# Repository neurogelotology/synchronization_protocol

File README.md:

# Synchronization Protocol

This repository provides files associated with our protocol paper about signal synchronization.

Dagher & Ishiyama (2023) STAR Protocols.

Example data are available:

Dagher, Sarah; Ishiyama, Shimpei (2023), “Signal synchronization in systems neuroscience (example data)”, Mendeley Data, V1, doi: 10.17632/98rzkwy8s6.1

## Pulse generator PCB

Printed circuit board (PCB) of the pulse generator is provided as KiCad files in the Pulse_Generator_PCB folder.

Printing the PCB can be outsourced to companies such as Aisler. Aisler accepts KiCad files directly.

## Pulse generator software

Codes necessary for the pulse generator are under the Pulse_Generator_software folder.

MATLAB files are necessary to trigger the pulse generator from MATLAB.

**exampleTimer.m** demonstrates an example use of triggering the pulse generator from MATLAB.

ArduinoLibrary\pulseGen folder contains Arduino files to setup the main Teensy board of the pulse generator.

myPulses folder contains an Arduino file to configure custom settings for each channel of the pulse generator.

## Sync TTL analysis

syncTTL folder contains MATLAB functions to extract TTL times from each signal.

**getAudioTTL_demo.m** extracts TTL rise times [s] from the least significant bit of a .wav file recorded by Avisoft devices. Times are based on the sample positions in the .wav file.

**getNlxTTL_demo.m**  extracts TTL rise times [s] from a Events.nev file created by Neuralynx Cheetah software. Users may need to adjust `TTLeventID` and `bitpos` dependent on the Neuralynx device used. Times are based on the timestamps of the Neuralynx device.

**getVideoTTL_demo.m** extracts TTL rise times [s] from a .csv file created by Bonsai with our configuration for the FLIR cameras. Times are based on the timestamps of the FLIR camera.

**sync_pulse_analysis.mlx** demonstrates sync pulse analysis to verify the validity of a recording. Example data are provided in Example_data folder.

## Bonsai file

**TwoCam.bonsai** demonstrates an example setting for video recording with two FLIR cameras, monitoring real-time TTL status and drop frames, embedding frame ID in the video frames, and exporting timestamp and TTL status of each frame as .csv files.

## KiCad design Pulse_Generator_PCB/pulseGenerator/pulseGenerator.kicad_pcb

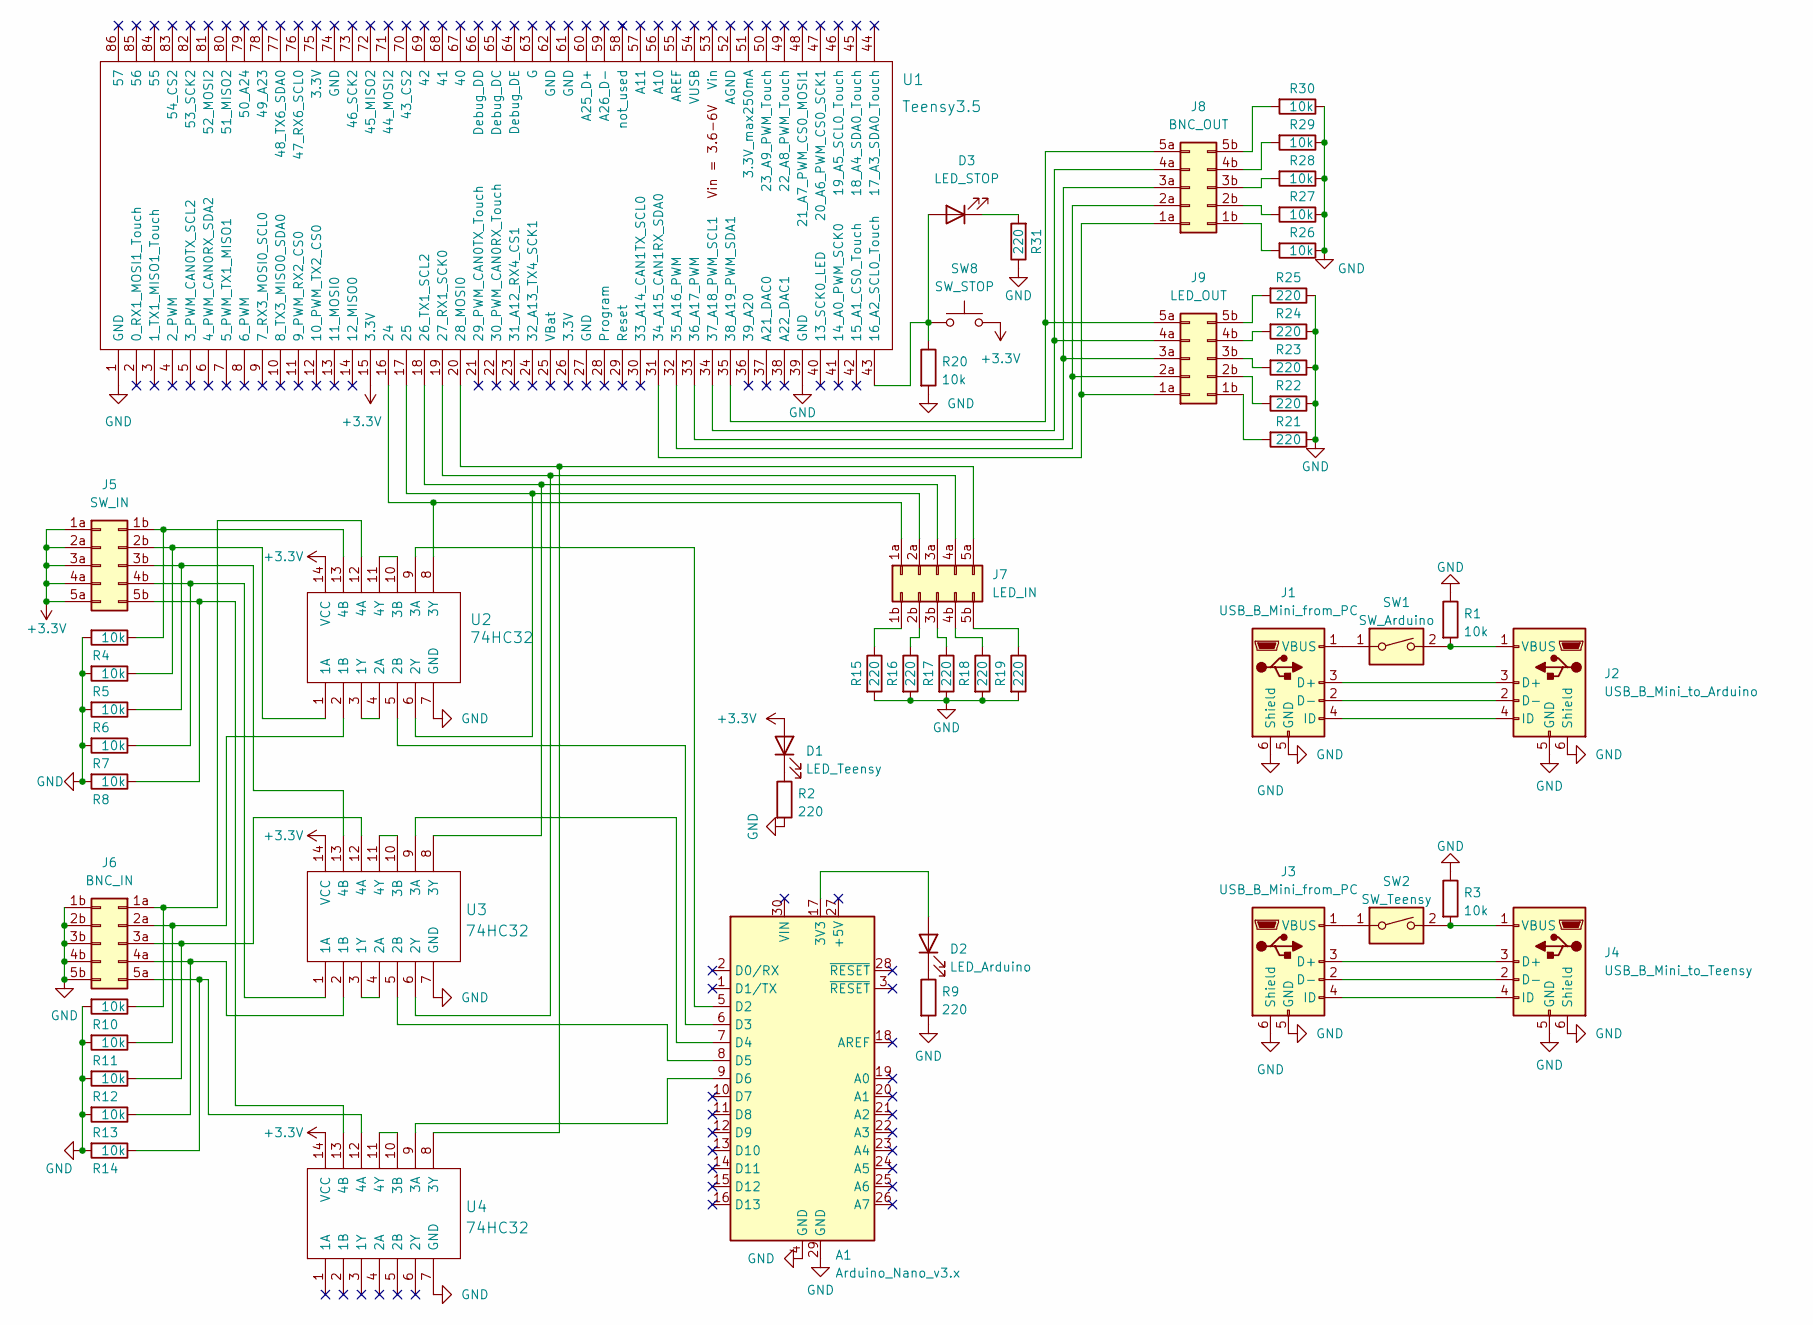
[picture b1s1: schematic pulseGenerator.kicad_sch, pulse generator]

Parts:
A1: Arduino_Nano_v3.x; Arduino_Nano
D1: LED_Teensy; PinHeader_1x02_P2.54mm_Vertical
D2: LED_Arduino; PinHeader_1x02_P2.54mm_Vertical
D3: LED_STOP; PinHeader_1x02_P2.54mm_Vertical
J1, J3: USB_B_Mini_from_PC; Micro_USB_Breakout
J2: USB_B_Mini_to_Arduino; Micro_USB_Breakout
J4: USB_B_Mini_to_Teensy; Micro_USB_Breakout
J5: SW_IN; PinHeader_2x05_P2.54mm_Vertical_row_letter_last
J6: BNC_IN; PinHeader_2x05_P2.54mm_Vertical_row_letter_last
J7: LED_IN; PinHeader_2x05_P2.54mm_Vertical_row_letter_last
J8: BNC_OUT; PinHeader_2x05_P2.54mm_Vertical_row_letter_last
J9: LED_OUT; PinHeader_2x05_P2.54mm_Vertical_row_letter_last
R1, R3, R4, R5, R6, R7, R8, R10, R11, R12, R13, R14, R20, R26, R27, R28, R29, R30: 10k; R_Axial_DIN0204_L3.6mm_D1.6mm_P5.08mm_Horizontal
R2, R9, R15, R16, R17, R18, R19, R21, R22, R23, R24, R25, R31: 220; R_Axial_DIN0204_L3.6mm_D1.6mm_P5.08mm_Horizontal
SW1: SW_Arduino; PinHeader_1x02_P2.54mm_Vertical
SW2: SW_Teensy; PinHeader_1x02_P2.54mm_Vertical
SW8: SW_STOP; PinHeader_1x02_P2.54mm_Vertical
U1: Teensy3.5
U2, U3, U4: 74HC32; DIP-14_W7.62mm

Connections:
+3.3V: D1.2 (A), J5.1a, J5.2a, J5.3a, J5.4a, J5.5a, SW8.2, U1.15 (3.3V), U2.14 (VCC), U3.14 (VCC), U4.14 (VCC)
GND: A1.4 (GND), A1.29 (GND), J1.5 (GND), J1.6 (Shield), J2.5 (GND), J2.6 (Shield), J3.5 (GND), J3.6 (Shield), J4.5 (GND), J4.6 (Shield), J6.1b, J6.2b, J6.3b, J6.4b, J6.5b, R1.1, R2.2, R3.1, R4.2, R5.2, R6.2, R7.2, R8.2, R9.2, R10.2, R11.2, R12.2, R13.2, R14.2, R15.2, R16.2, R17.2, R18.2, R19.2, R20.2, R21.1, R22.1, R23.1, R24.1, R25.1, R26.1, R27.1, R28.1, R29.1, R30.1, R31.1, U1.1 (GND), U1.39 (GND), U2.7 (GND), U3.7 (GND), U4.7 (GND)
unnamed: A1.5 (D2), U2.9 (3A)
unnamed: A1.6 (D3), U2.5 (2B)
unnamed: A1.7 (D4), U3.9 (3A)
unnamed: A1.8 (D5), U3.5 (2B)
unnamed: A1.9 (D6), U4.9 (3A)
unnamed: A1.17 (3V3), D2.2 (A)
unnamed: D1.1 (K), R2.1
unnamed: D2.1 (K), R9.1
unnamed: D3.1 (K), R31.2
unnamed: J1.1 (VBUS), SW1.1
unnamed: J1.2 (D-), J2.2 (D-)
unnamed: J1.3 (D+), J2.3 (D+)
unnamed: J1.4 (ID), J2.4 (ID)
unnamed: J2.1 (VBUS), R1.2, SW1.2
unnamed: J3.1 (VBUS), SW2.1
unnamed: J3.2 (D-), J4.2 (D-)
unnamed: J3.3 (D+), J4.3 (D+)
unnamed: J3.4 (ID), J4.4 (ID)
unnamed: J4.1 (VBUS), R3.2, SW2.2
unnamed: J7.1b, R15.1
unnamed: J7.2b, R16.1
unnamed: J7.3b, R17.1
unnamed: J7.4b, R18.1
unnamed: J7.5b, R19.1
unnamed: J8.1b, R26.2
unnamed: J8.2b, R27.2
unnamed: J8.3b, R28.2
unnamed: J8.4b, R29.2
unnamed: J8.5b, R30.2
unnamed: J9.1b, R21.2
unnamed: J9.2b, R22.2
unnamed: J9.3b, R23.2
unnamed: J9.4b, R24.2
unnamed: J9.5b, R25.2
unnamed: D3.2 (A), R20.1, SW8.1, U1.43 (16_A2_SCL0_Touch)
unnamed: J7.1a, U1.16 (24), U2.8 (3Y)
unnamed: J7.2a, U1.17 (25), U2.6 (2Y)
unnamed: J7.3a, U1.18 (26_TX1_SCL2), U3.8 (3Y)
unnamed: J7.4a, U1.19 (27_RX1_SCK0), U3.6 (2Y)
unnamed: J7.5a, U1.20 (28_MOSI0), U4.8 (3Y)
unnamed: J8.1a, J9.1a, U1.31 (34_A15_CAN1RX_SDA0)
unnamed: J8.2a, J9.2a, U1.32 (35_A16_PWM)
unnamed: J8.3a, J9.3a, U1.33 (36_A17_PWM)
unnamed: J8.4a, J9.4a, U1.34 (37_A18_PWM_SCL1)
unnamed: J8.5a, J9.5a, U1.35 (38_A19_PWM_SDA1)
unnamed: J5.2b, R5.1, U2.1 (1A)
unnamed: J6.2a, R11.1, U2.2 (1B)
unnamed: U2.3 (1Y), U2.4 (2A)
unnamed: U2.10 (3B), U2.11 (4Y)
unnamed: J6.1a, R10.1, U2.12 (4A)
unnamed: J5.1b, R4.1, U2.13 (4B)
unnamed: J5.4b, R7.1, U3.1 (1A)
unnamed: J6.4a, R13.1, U3.2 (1B)
unnamed: U3.3 (1Y), U3.4 (2A)
unnamed: U3.10 (3B), U3.11 (4Y)
unnamed: J6.3a, R12.1, U3.12 (4A)
unnamed: J5.3b, R6.1, U3.13 (4B)
unnamed: U4.10 (3B), U4.11 (4Y)
unnamed: J6.5a, R14.1, U4.12 (4A)
unnamed: J5.5b, R8.1, U4.13 (4B)

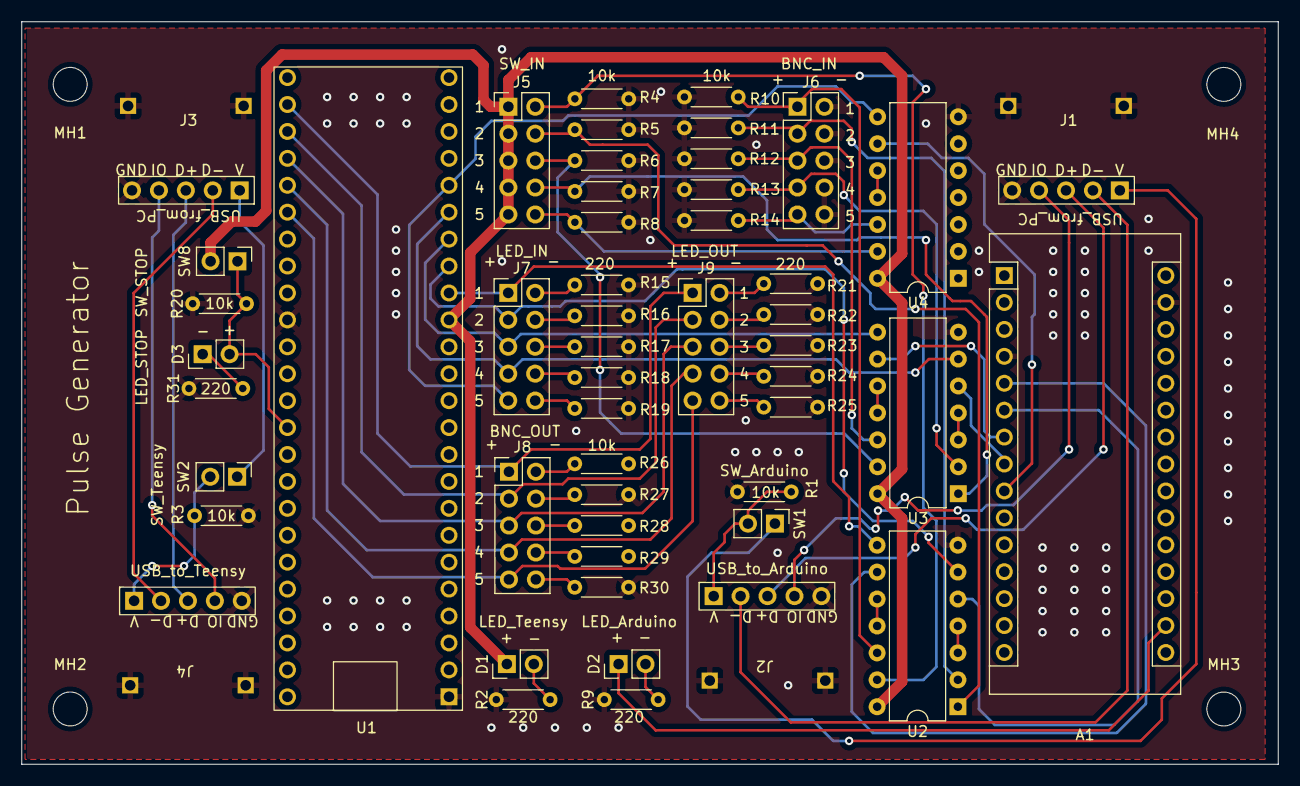
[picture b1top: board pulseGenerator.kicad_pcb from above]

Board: 2 copper layers, 118.6 x 70.1 mm, 55 parts (0 on the bottom side), 62 nets.

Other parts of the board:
MH1, MH2, MH3, MH4: MountingHole_3.2mm_M3

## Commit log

2023-04-18 Add all necessary files.
